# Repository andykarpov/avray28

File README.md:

PCB (DIP28 version) for the AY AVR Emulator on Atmega8A

This PCB is based on the avray.ru project sources and tech documentation.

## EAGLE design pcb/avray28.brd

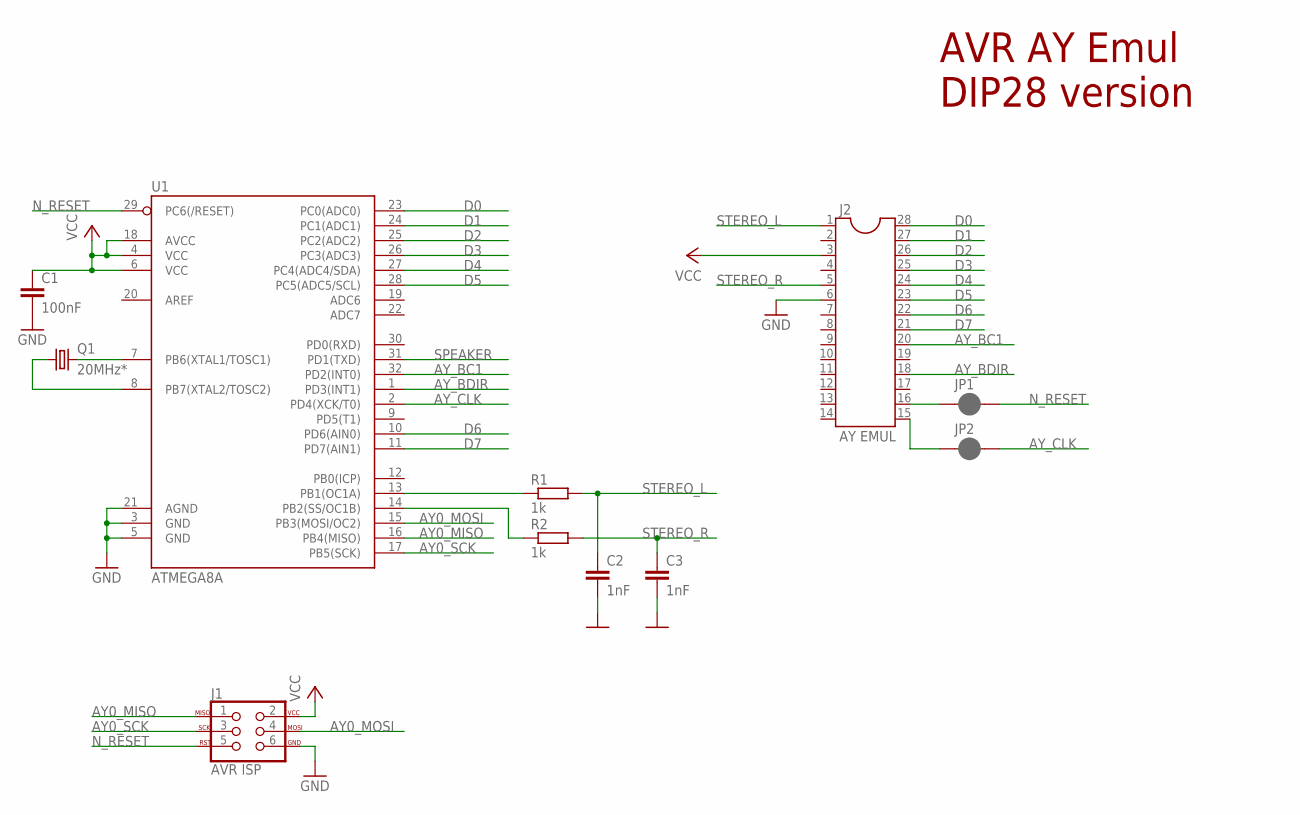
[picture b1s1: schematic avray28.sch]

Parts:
C1: 100nF; C0805
C2, C3: 1nF; C0805
J1: AVR ISP; 2X3_LOCK
J2: AY EMUL; DIL28-6
JP1: RST ENA; SMT-JUMPER_2_NC_PASTE_SILK
JP2: CLK ENA; SMT-JUMPER_2_NC_PASTE_SILK
Q1: 20MHz*; HC49/S
R1, R2: 1k; R0805
U1: ATMEGA8A; TQFP32-08

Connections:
AY0_MISO: J1.1, U1.16 (PB4(MISO))
AY0_MOSI: J1.4, U1.15 (PB3(MOSI/OC2))
AY0_SCK: J1.3, U1.17 (PB5(SCK))
AY_BC1: J2.20, U1.32 (PD2(INT0))
AY_BDIR: J2.18, U1.1 (PD3(INT1))
AY_CLK: JP2.2, U1.2 (PD4(XCK/T0))
D0: J2.28, U1.23 (PC0(ADC0))
D1: J2.27, U1.24 (PC1(ADC1))
D2: J2.26, U1.25 (PC2(ADC2))
D3: J2.25, U1.26 (PC3(ADC3))
D4: J2.24, U1.27 (PC4(ADC4/SDA))
D5: J2.23, U1.28 (PC5(ADC5/SCL))
D6: J2.22, U1.10 (PD6(AIN0))
D7: J2.21, U1.11 (PD7(AIN1))
GND: C1.2, C2.2, C3.2, J1.6, J2.6, U1.3 (GND), U1.5 (GND), U1.21 (AGND)
unnamed: J2.16, JP1.1
unnamed: J2.15, JP2.1
unnamed: R1.1, U1.13 (PB1(OC1A))
unnamed: R2.1, U1.14 (PB2(SS/OC1B))
unnamed: Q1.2, U1.7 (PB6(XTAL1/TOSC1))
unnamed: Q1.1, U1.8 (PB7(XTAL2/TOSC2))
N_RESET: J1.5, JP1.2, U1.29 (PC6(/RESET))
SPEAKER: U1.31 (PD1(TXD))
STEREO_L: C2.1, J2.1, R1.2
STEREO_R: C3.1, J2.5, R2.2
VCC: C1.1, J1.2, J2.3, U1.4 (VCC), U1.6 (VCC), U1.18 (AVCC)

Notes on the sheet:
AVR AY Emul DIP28 version

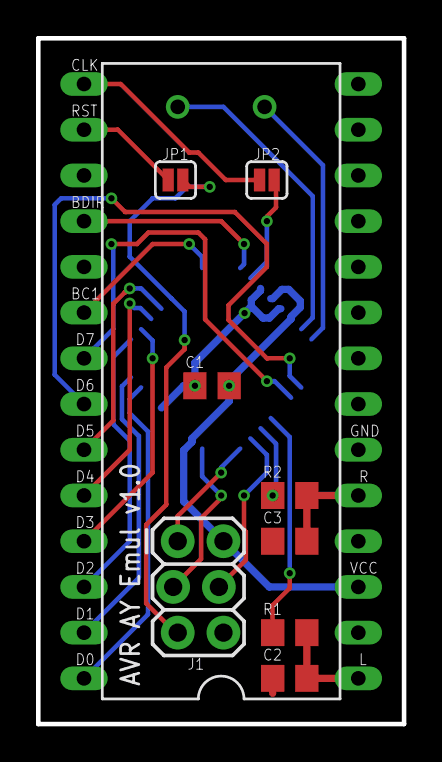
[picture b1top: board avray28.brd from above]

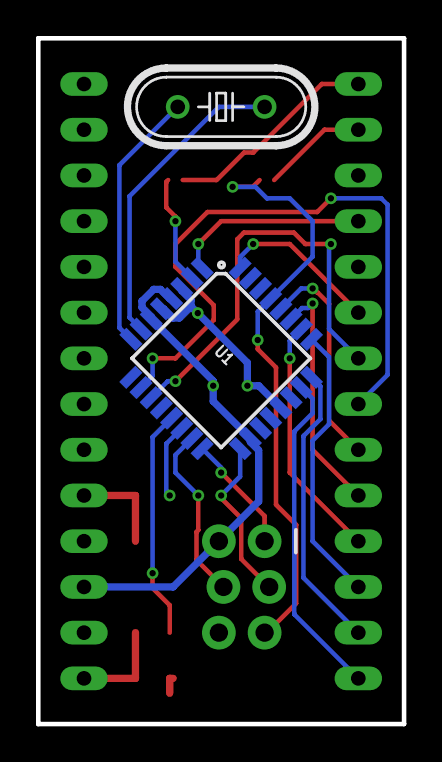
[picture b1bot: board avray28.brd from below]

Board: 2 copper layers, 20.3 x 38.1 mm, 11 parts (2 on the bottom side), 25 nets.

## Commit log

2019-09-27 initial version

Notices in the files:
parts and their libraries:
SparkFun-IC-Microcontroller: Licensing: Creative Commons ShareAlike 4.0 International - https://creativecommons.org/licenses/by-sa/4.0
